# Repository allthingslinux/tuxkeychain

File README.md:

# Tux Keychain
Keychain shaped like Tux, the Linux mascot. But it's not just a keychain, it runs embedded Linux!

Unfortunately this is more expensive than usual due to tariffs and inflation. (Probably cheaper in other countries.)

NOTE: This is still in the prototype stage, changes to the design are likely.

## Manufacturing
- This is a 4-layer PCB so it can fit in the Tux keychain form factor.
- Make sure you use ENIG for the PCB finish, else Tux will be gray instead of gold. (If you want a gray Tux, seek help.)
- This is designed for JLCPCBs assembly service, some parts are LCSC exclusive*.

*You can probably find them on other chinese distributors, but I don't know which ones.

## Attribution
The Allwinner F1C100s footprint/symbol is from https://github.com/thirtythreeforty/3340_kicad (F1C100s symbol, QFN-88_EP_10x10_Pitch0.4mm footprint).
Same for the JW5211 symbol and footprint.

Schematic heavily based on the business card design by thirtythreeforty (https://www.thirtythreeforty.net/posts/2019/12/my-business-card-runs-linux/businesscard.pdf).

Tux attribution: [lewing@isc.tamu.edu](https://isc.tamu.edu/~lewing/linux/) (Larry Ewing) and [The GIMP](https://www.gimp.org/).

## Images
> [!NOTE]
> These are auto-generated and will always be up to date (GitHub cache may make them seem out of date)

|PCB|Schematic|
|---|---|
|||
|||

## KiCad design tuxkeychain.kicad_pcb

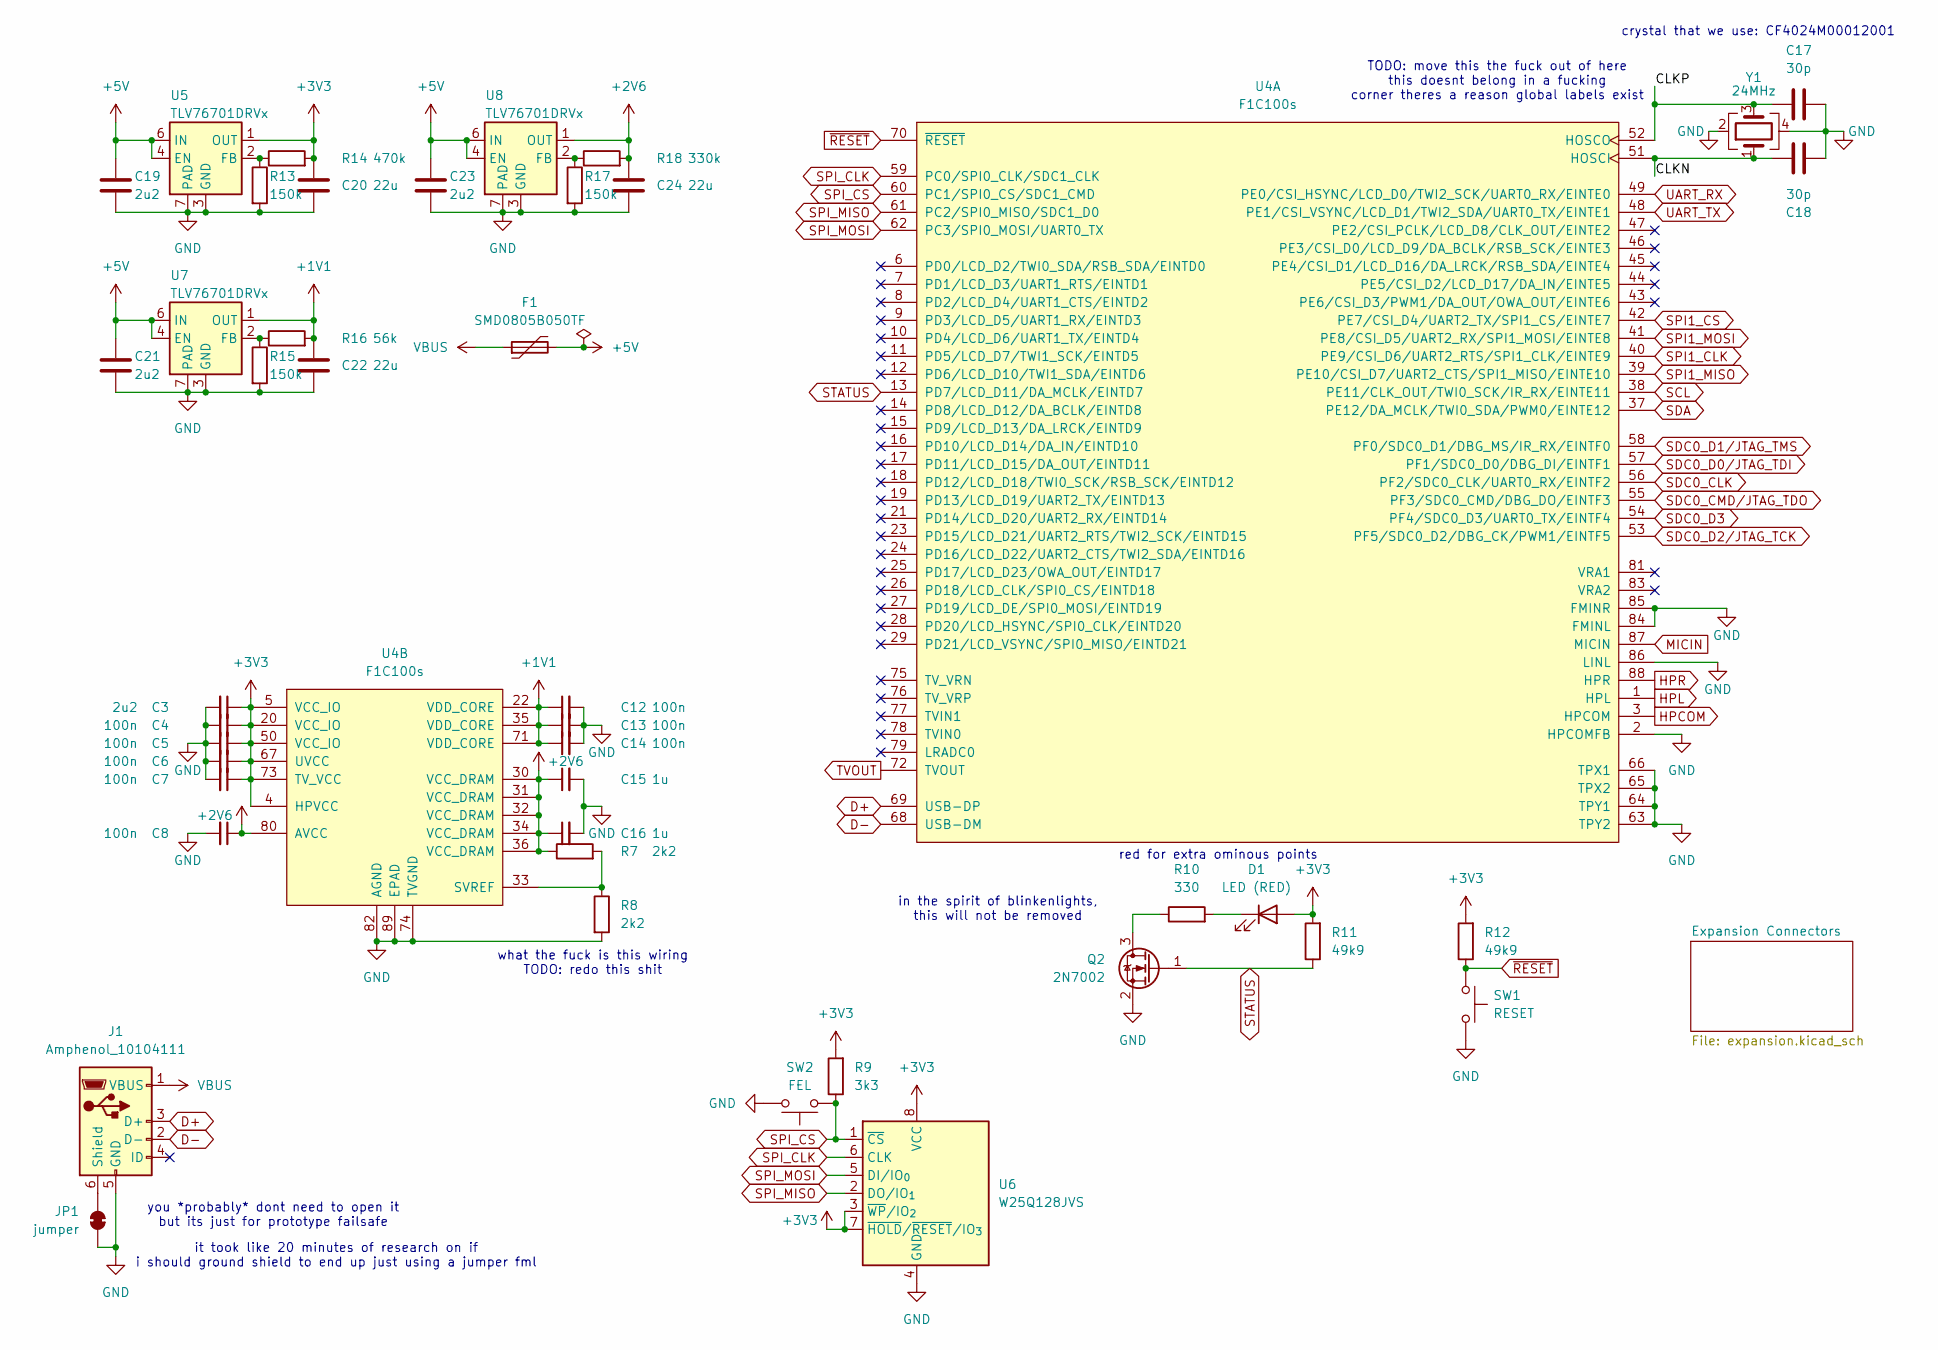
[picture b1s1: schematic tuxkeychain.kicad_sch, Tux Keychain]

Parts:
C3, C19, C21, C23: 2u2; C_0402_1005Metric
C4, C5, C6, C7, C8, C12, C13, C14: 100n; C_0402_1005Metric
C15, C16: 1u; C_0402_1005Metric
C17, C18: 30p; C_0402_1005Metric
C20, C22, C24: 22u; C_0402_1005Metric
D1: LED (RED); LED_0603_1608Metric
F1: SMD0805B050TF; Fuse_0805_2012Metric
J1: Amphenol_10104111; CONN_10104111-0001LF_AMP
JP1: jumper; SolderJumper-2_P1.3mm_Bridged_RoundedPad1.0x1.5mm
Q2: 2N7002; SOT-23
R7, R8: 2k2; R_0402_1005Metric
R9: 3k3; R_0402_1005Metric
R10: 330; R_0402_1005Metric
R11, R12: 49k9; R_0402_1005Metric
R13, R15, R17: 150k; R_0402_1005Metric
R14: 470k; R_0402_1005Metric
R16: 56k; R_0402_1005Metric
R18: 330k; R_0402_1005Metric
SW1: RESET; SW_SPST_B3U-1000P
SW2: FEL; SW_SPST_B3U-1000P
U4: F1C100s; QFN-88_EP_10x10_Pitch0.4mm
U5, U7, U8: TLV76701DRVx; WSON-6-1EP_2x2mm_P0.65mm_EP1x1.6mm
U6: W25Q128JVS; SOIC-8_5.3x5.3mm_P1.27mm
Y1: 24MHz; Crystal_SMD_3225-4Pin_3.2x2.5mm

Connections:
+1V1: C12.1, C13.1, C14.1, C22.1, R16.2, U4.22 (VDD_CORE), U4.35 (VDD_CORE), U4.71 (VDD_CORE), U7.1 (OUT); also elsewhere on the board
+2V6: C8.1, C15.1, C16.1, C24.1, R7.1, R18.2, U4.30 (VCC_DRAM), U4.31 (VCC_DRAM), U4.32 (VCC_DRAM), U4.34 (VCC_DRAM), U4.36 (VCC_DRAM), U4.80 (AVCC), U8.1 (OUT); also elsewhere on the board
+3V3: C3.1, C4.1, C5.1, C6.1, C7.1, C20.1, D1.2 (A), R9.2, R11.2, R12.2, R14.2, U4.4 (HPVCC), U4.5 (VCC_IO), U4.20 (VCC_IO), U4.50 (VCC_IO), U4.67 (UVCC), U4.73 (TV_VCC), U5.1 (OUT), U6.3 (~WP/IO_{2}), U6.7 (~HOLD/~RESET/IO_{3}), U6.8 (VCC); also elsewhere on the board
+5V: C19.1, C21.1, C23.1, F1.2, U5.4 (EN), U5.6 (IN), U7.4 (EN), U7.6 (IN), U8.4 (EN), U8.6 (IN); also elsewhere on the board
/CLKN: C18.1, U4.51 (HOSCI), Y1.1
/CLKP: C17.1, U4.52 (HOSCO), Y1.3
D+: J1.3 (D+), U4.69 (USB-DP)
D-: J1.2 (D-), U4.68 (USB-DM)
GND: C3.2, C4.2, C5.2, C6.2, C7.2, C8.2, C12.2, C13.2, C14.2, C15.2, C16.2, C17.2, C18.2, C19.2, C20.2, C21.2, C22.2, C23.2, C24.2, J1.5 (GND), JP1.1 (A), Q2.2 (S), R8.2, R13.2, R15.2, R17.2, SW1.2, SW2.2, U4.2 (HPCOMFB), U4.63 (TPY2), U4.64 (TPY1), U4.65 (TPX2), U4.66 (TPX1), U4.74 (TVGND), U4.82 (AGND), U4.84 (FMINL), U4.85 (FMINR), U4.86 (LINL), U4.89 (EPAD), U5.3 (GND), U5.5 (GND), U5.7 (PAD), U6.4 (GND), U7.3 (GND), U7.5 (GND), U7.7 (PAD), U8.3 (GND), U8.5 (GND), U8.7 (PAD), Y1.2, Y1.4; also elsewhere on the board
HPCOM: U4.3 (HPCOM); also elsewhere on the board
HPL: U4.1 (HPL); also elsewhere on the board
HPR: U4.88 (HPR); also elsewhere on the board
MICIN: U4.87 (MICIN); also elsewhere on the board
unnamed: D1.1 (K), R10.2
unnamed: J1.6 (Shield), JP1.2 (B)
unnamed: Q2.3 (D), R10.1
unnamed: R7.2, R8.1, U4.33 (SVREF)
unnamed: R13.1, R14.1, U5.2 (FB)
unnamed: R15.1, R16.1, U7.2 (FB)
unnamed: R17.1, R18.1, U8.2 (FB)
SCL: U4.38 (PE11/CLK_OUT/TWI0_SCK/IR_RX/EINTE11); also elsewhere on the board
SDA: U4.37 (PE12/DA_MCLK/TWI0_SDA/PWM0/EINTE12); also elsewhere on the board
SDC0_CLK: U4.56 (PF2/SDC0_CLK/UART0_RX/EINTF2); also elsewhere on the board
SDC0_CMD/JTAG_TDO: U4.55 (PF3/SDC0_CMD/DBG_DO/EINTF3); also elsewhere on the board
SDC0_D0/JTAG_TDI: U4.57 (PF1/SDC0_D0/DBG_DI/EINTF1); also elsewhere on the board
SDC0_D1/JTAG_TMS: U4.58 (PF0/SDC0_D1/DBG_MS/IR_RX/EINTF0); also elsewhere on the board
SDC0_D2/JTAG_TCK: U4.53 (PF5/SDC0_D2/DBG_CK/PWM1/EINTF5); also elsewhere on the board
SDC0_D3: U4.54 (PF4/SDC0_D3/UART0_TX/EINTF4); also elsewhere on the board
SPI1_CLK: U4.40 (PE9/CSI_D6/UART2_RTS/SPI1_CLK/EINTE9); also elsewhere on the board
SPI1_CS: U4.42 (PE7/CSI_D4/UART2_TX/SPI1_CS/EINTE7); also elsewhere on the board
SPI1_MISO: U4.39 (PE10/CSI_D7/UART2_CTS/SPI1_MISO/EINTE10); also elsewhere on the board
SPI1_MOSI: U4.41 (PE8/CSI_D5/UART2_RX/SPI1_MOSI/EINTE8); also elsewhere on the board
SPI_CLK: U4.59 (PC0/SPI0_CLK/SDC1_CLK), U6.6 (CLK)
SPI_CS: R9.1, SW2.1, U4.60 (PC1/SPI0_CS/SDC1_CMD), U6.1 (~CS)
SPI_MISO: U4.61 (PC2/SPI0_MISO/SDC1_D0), U6.2 (DO/IO_{1})
SPI_MOSI: U4.62 (PC3/SPI0_MOSI/UART0_TX), U6.5 (DI/IO_{0})
STATUS: Q2.1 (G), R11.1, U4.13 (PD7/LCD_D11/DA_MCLK/EINTD7)
TVOUT: U4.72 (TVOUT); also elsewhere on the board
UART_RX: U4.49 (PE0/CSI_HSYNC/LCD_D0/TWI2_SCK/UART0_RX/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); also elsewhere on the board
UART_TX: U4.48 (PE1/CSI_VSYNC/LCD_D1/TWI2_SDA/UART0_TX/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); also elsewhere on the board
VBUS: F1.1, J1.1 (VBUS)
~RESET: R12.1, SW1.1, U4.70 (~RESET)

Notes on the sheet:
red for extra ominous points
in the spirit of blinkenlights, this will not be removed
it took like 20 minutes of research on if i should ground shield to end up just using a jumper fml
crystal that we use: CF4024M00012001
you *probably* dont need to open it but its just for prototype failsafe
what the fuck is this wiring TODO: redo this shit
TODO: move this the fuck out of here this doesnt belong in a fucking corner theres a reason global labels exist

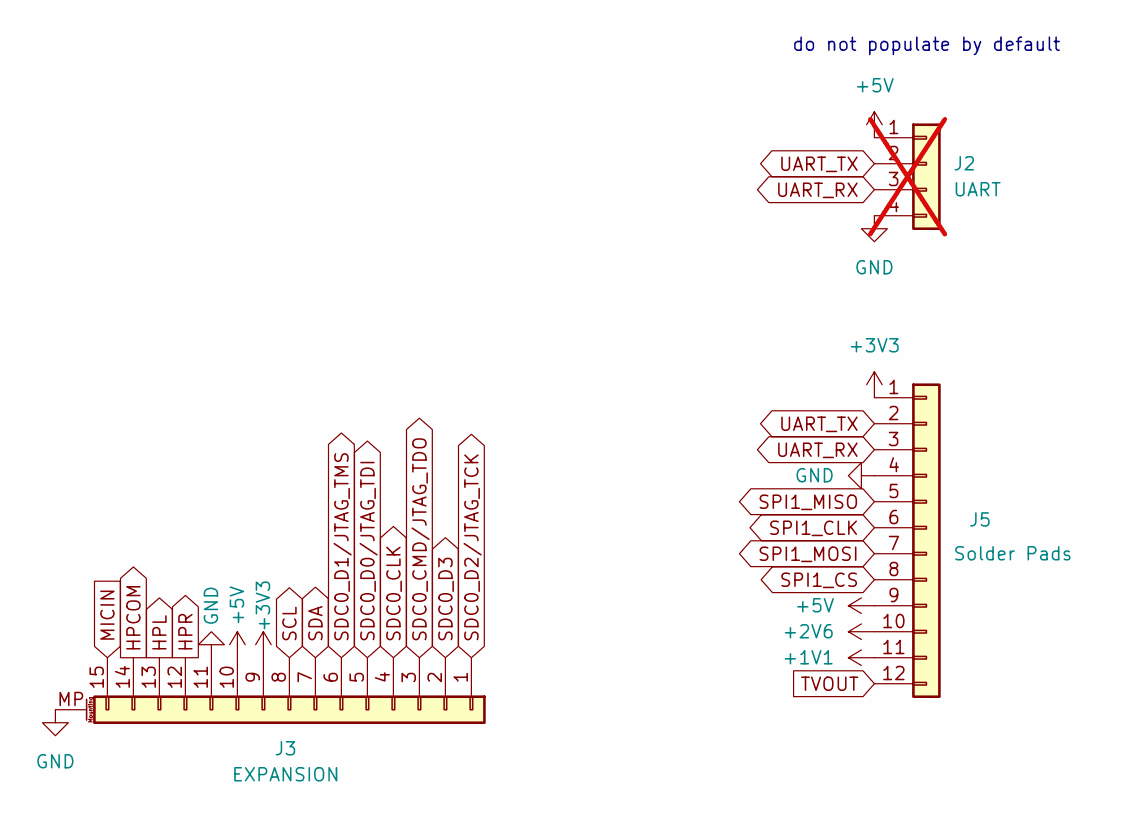
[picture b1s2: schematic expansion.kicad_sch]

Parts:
J2: UART; PinHeader_1x04_P2.54mm_Vertical_SMD_Pin1Left; not fitted
J3: EXPANSION; Jushuo_AFC07-S15FCA-00_1x15-1MP_P0.50_Horizontal
J5: Solder Pads; SolderPads12

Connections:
+1V1: J5.11; also elsewhere on the board
+2V6: J5.10; also elsewhere on the board
+3V3: J3.9, J5.1; also elsewhere on the board
+5V: J2.1, J3.10, J5.9; also elsewhere on the board
GND: J2.4, J3.11, J3.MP (MountPin), J5.4; also elsewhere on the board
HPCOM: J3.14; also elsewhere on the board
HPL: J3.13; also elsewhere on the board
HPR: J3.12; also elsewhere on the board
MICIN: J3.15; also elsewhere on the board
SCL: J3.8; also elsewhere on the board
SDA: J3.7; also elsewhere on the board
SDC0_CLK: J3.4; also elsewhere on the board
SDC0_CMD/JTAG_TDO: J3.3; also elsewhere on the board
SDC0_D0/JTAG_TDI: J3.5; also elsewhere on the board
SDC0_D1/JTAG_TMS: J3.6; also elsewhere on the board
SDC0_D2/JTAG_TCK: J3.1; also elsewhere on the board
SDC0_D3: J3.2; also elsewhere on the board
SPI1_CLK: J5.6; also elsewhere on the board
SPI1_CS: J5.8; also elsewhere on the board
SPI1_MISO: J5.5; also elsewhere on the board
SPI1_MOSI: J5.7; also elsewhere on the board
TVOUT: J5.12; also elsewhere on the board
UART_RX: J2.3, J5.3; also elsewhere on the board
UART_TX: J2.2, J5.2; also elsewhere on the board

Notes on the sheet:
do not populate by default

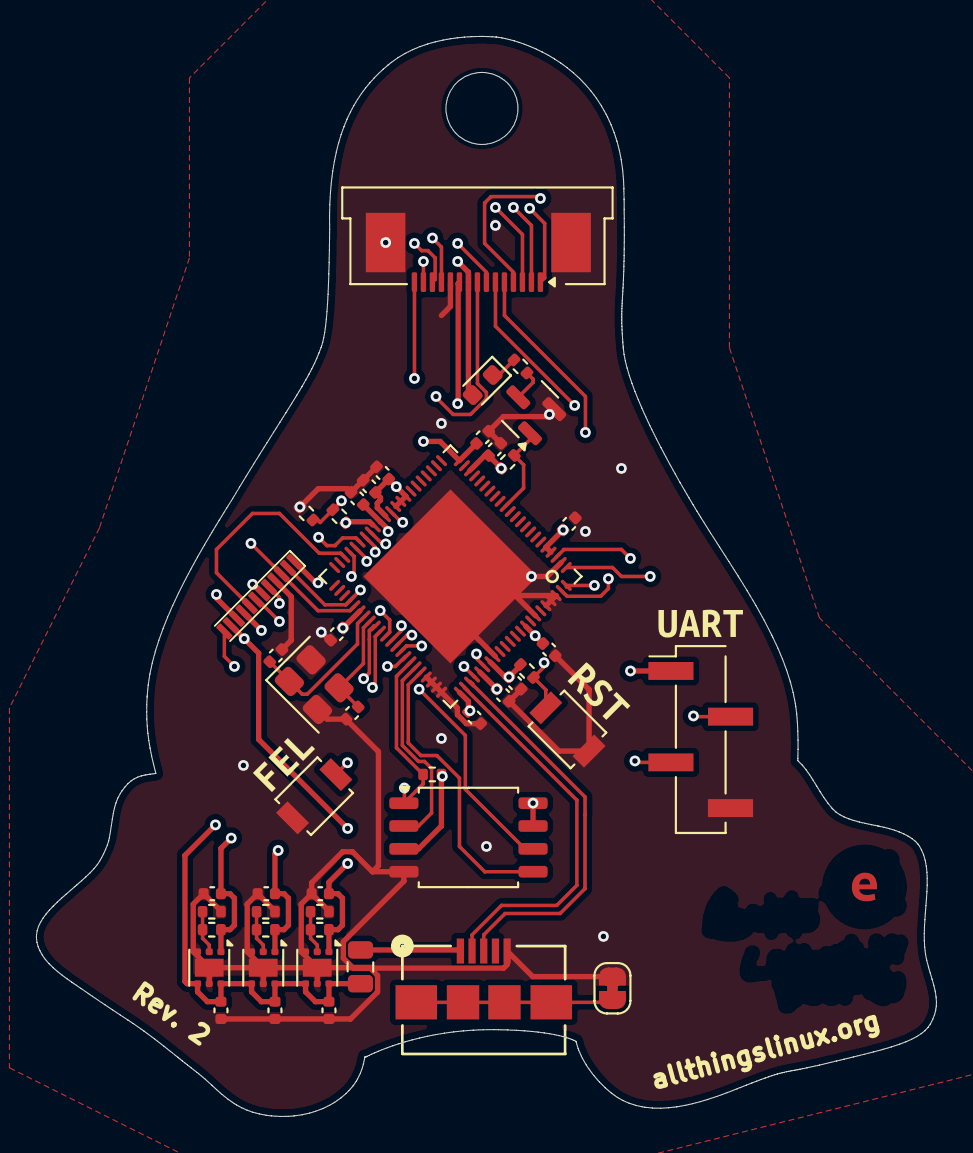
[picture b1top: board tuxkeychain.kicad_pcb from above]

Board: 6 copper layers, 50.0 x 60.0 mm, 53 parts (3 on the bottom side), 42 nets.

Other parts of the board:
GRAPHIC1: DrillHole
GRAPHIC2, GRAPHIC3: Graphics
kibuzzard-687B569F: G***; kibuzzard-687B569F
kibuzzard-687B5666: G***; kibuzzard-687B5666
kibuzzard-688DDBDB: G***; kibuzzard-688DDBDB

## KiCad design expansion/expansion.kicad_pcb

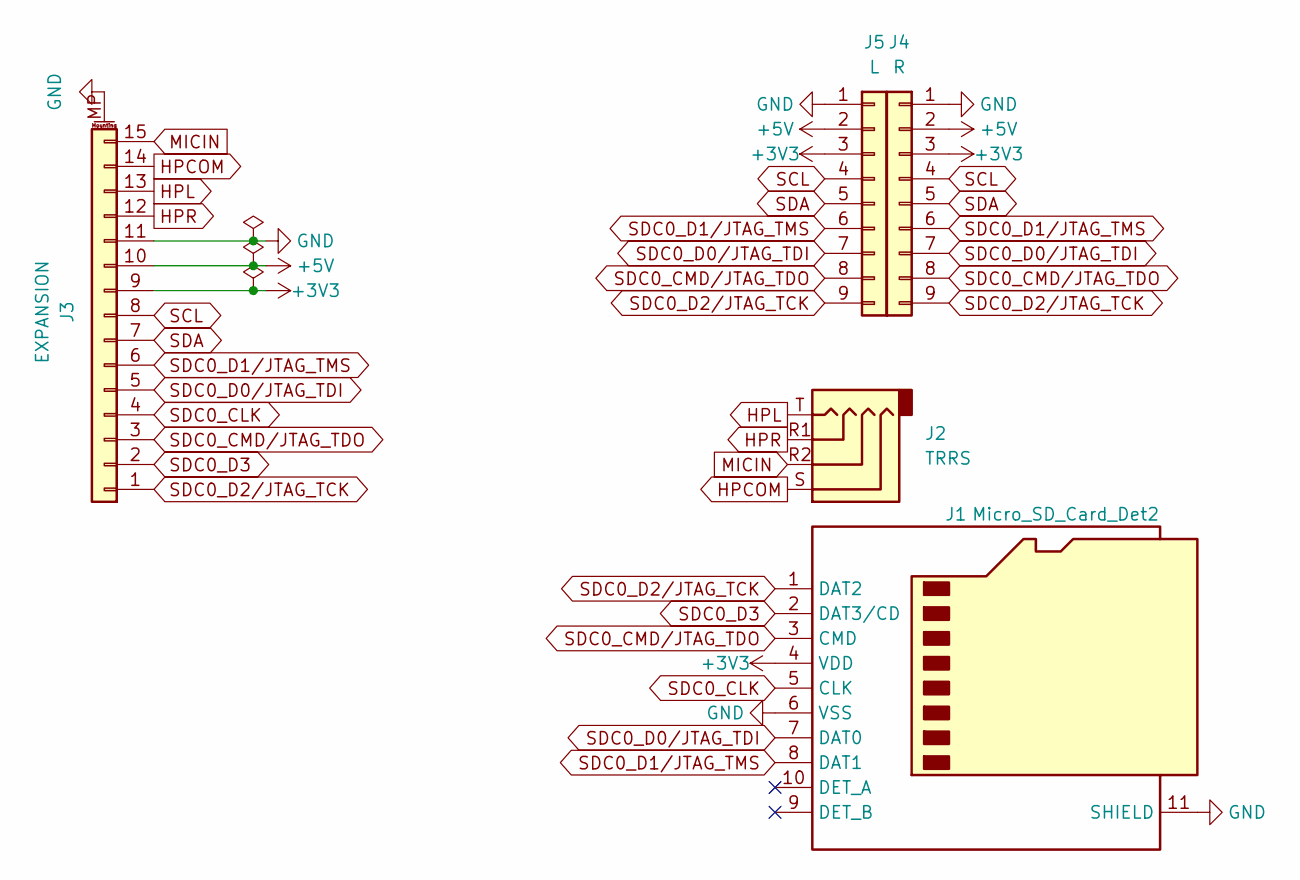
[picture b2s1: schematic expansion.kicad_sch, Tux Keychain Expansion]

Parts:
J1: Micro_SD_Card_Det2; microSD_HC_Molex_104031-0811
J2: TRRS; Jack_3.5mm_KoreanHropartsElec_PJ-320D-4A_Horizontal
J3: EXPANSION; FFC_1x15_P0.5mm
J4: R; PinHeader_1x09_P2.54mm_Vertical
J5: L; PinHeader_1x09_P2.54mm_Vertical

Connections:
+3V3: J1.4 (VDD), J3.9, J4.3, J5.3
+5V: J3.10, J4.2, J5.2
GND: J1.6 (VSS), J1.11 (SHIELD), J3.11, J3.MP (MountPin), J4.1, J5.1
HPCOM: J2.S, J3.14
HPL: J2.T, J3.13
HPR: J2.R1, J3.12
MICIN: J2.R2, J3.15
SCL: J3.8, J4.4, J5.4
SDA: J3.7, J4.5, J5.5
SDC0_CLK: J1.5 (CLK), J3.4
SDC0_CMD/JTAG_TDO: J1.3 (CMD), J3.3, J4.8, J5.8
SDC0_D0/JTAG_TDI: J1.7 (DAT0), J3.5, J4.7, J5.7
SDC0_D1/JTAG_TMS: J1.8 (DAT1), J3.6, J4.6, J5.6
SDC0_D2/JTAG_TCK: J1.1 (DAT2), J3.1, J4.9, J5.9
SDC0_D3: J1.2 (DAT3/CD), J3.2

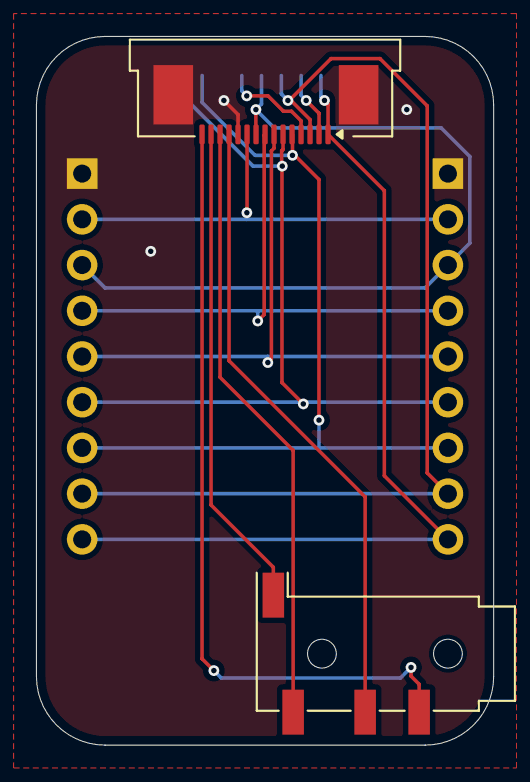
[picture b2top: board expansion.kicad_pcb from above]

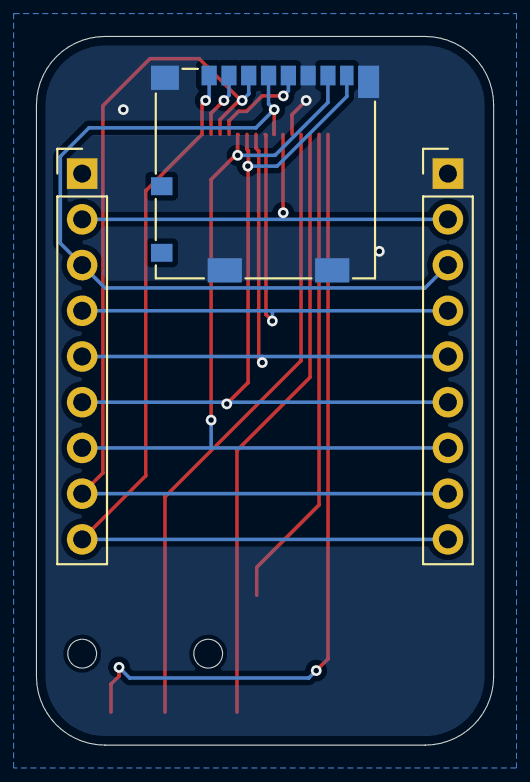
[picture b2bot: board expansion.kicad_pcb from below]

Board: 2 copper layers, 25.4 x 39.4 mm, 5 parts (3 on the bottom side), 15 nets.

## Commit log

2025-05-22 Change regulators to the TLV76701DRVx due to supply chain issues
2025-05-22 Initial README change
2025-05-22 Add generated images
2025-05-22 Refactor KiCad workflow to use cached APT packages for installation
2025-05-22 Revert "Refactor KiCad workflow to use cached APT packages for installation"
    This reverts commit 15d390258ad1cd0148efe828dac26ec40c4fc02e.
2025-05-22 Refactor KiCad CI workflow to use cache-apt-pkgs-action for package installation
2025-05-22 bump rev
2025-05-22 Revert "bump rev"
    This reverts commit ef9e417096638242890c258b05ee16d024b64b77.
2025-05-22 bump rev (this time correctly)
2025-05-22 Update resistor values in schematic to standard E12 values
2025-05-22 rev 2
2025-05-23 imrptoravnemtn
2025-05-23 Added expansion connectors to schematic
2025-05-23 Added expansion connectors to pcb
2025-05-23 work
2025-05-23 more stuff
2025-05-23 stuff
2025-05-23 Fix installation issues in KiCad workflows
2025-05-23 hopefully make it faster
2025-05-23 full pbc layout completed
2025-05-24 Update SolderPads12 footprint attributes to exclude from position files and BOM
2025-05-24 Changed board to 6 layers, made appropriate routing changes
2025-05-25 minor trace cleanups
2025-05-25 fix drc
2025-05-25 fix name for footprint
2025-05-25 fix 3d model
2025-05-25 remove some logos and re hide references
2025-06-12 change led resistor and add FEL button
2025-07-09 Add renovate.json
2025-07-19 add labels for the rst/fel buttons
2025-07-19 change armv8 logo
2025-08-02 add uart header
2025-08-02 fixed some wonky traces
